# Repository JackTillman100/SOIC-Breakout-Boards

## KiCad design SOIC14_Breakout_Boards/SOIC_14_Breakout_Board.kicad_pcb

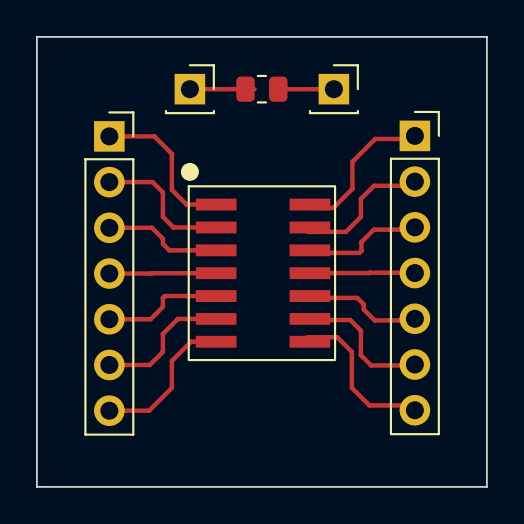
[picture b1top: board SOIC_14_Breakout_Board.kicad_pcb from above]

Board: 2 copper layers, 25.0 x 25.0 mm, 6 parts (0 on the bottom side), 16 nets.

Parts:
J1, J2: Conn_01x07; PinSocket_1x07_P2.54mm_Vertical
J3, J4: Conn_01x01; PinSocket_1x01_P2.54mm_Vertical
R1: R_US; R_0805_2012Metric
SOIC14: 14_Pin_SOIC_Board

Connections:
unnamed: J1.1, SOIC14.1
unnamed: J1.2, SOIC14.2
unnamed: J1.3, SOIC14.3
unnamed: J1.4, SOIC14.4
unnamed: J1.5, SOIC14.5
unnamed: J1.6, SOIC14.6
unnamed: J1.7, SOIC14.7
unnamed: J2.1, SOIC14.14
unnamed: J2.2, SOIC14.13
unnamed: J2.3, SOIC14.12
unnamed: J2.4, SOIC14.11
unnamed: J2.5, SOIC14.10
unnamed: J2.6, SOIC14.9
unnamed: J2.7, SOIC14.8
unnamed: J3.1, R1.2
unnamed: J4.1, R1.1

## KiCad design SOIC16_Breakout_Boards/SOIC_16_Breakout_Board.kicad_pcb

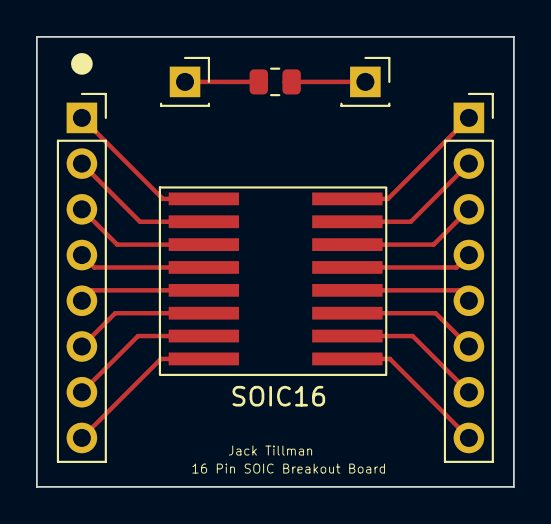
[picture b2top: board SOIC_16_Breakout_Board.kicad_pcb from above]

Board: 2 copper layers, 26.5 x 25.0 mm, 6 parts (0 on the bottom side), 18 nets.

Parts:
J1, J2: Conn_01x08; PinSocket_1x08_P2.54mm_Vertical
J3, J4: Conn_01x01; PinSocket_1x01_P2.54mm_Vertical
R1: R_US; R_0805_2012Metric
SOIC16: 16_Pin_SOIC_Board

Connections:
unnamed: J1.1, SOIC16.1
unnamed: J1.2, SOIC16.2
unnamed: J1.3, SOIC16.3
unnamed: J1.4, SOIC16.4
unnamed: J1.5, SOIC16.5
unnamed: J1.6, SOIC16.6
unnamed: J1.7, SOIC16.7
unnamed: J1.8, SOIC16.8
unnamed: J2.1, SOIC16.16
unnamed: J2.2, SOIC16.15
unnamed: J2.3, SOIC16.14
unnamed: J2.4, SOIC16.13
unnamed: J2.5, SOIC16.12
unnamed: J2.6, SOIC16.11
unnamed: J2.7, SOIC16.10
unnamed: J2.8, SOIC16.9
unnamed: J3.1, R1.2
unnamed: J4.1, R1.1

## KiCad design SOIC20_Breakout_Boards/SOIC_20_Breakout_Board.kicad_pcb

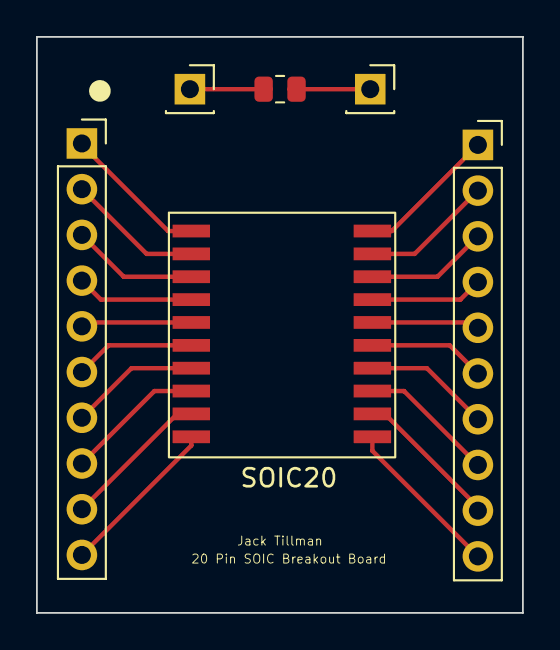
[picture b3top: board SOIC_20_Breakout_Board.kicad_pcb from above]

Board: 2 copper layers, 27.0 x 32.0 mm, 6 parts (0 on the bottom side), 22 nets.

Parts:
J1, J2: Conn_01x10; PinSocket_1x10_P2.54mm_Vertical
J3, J4: Conn_01x01; PinSocket_1x01_P2.54mm_Vertical
R1: R_US; R_0805_2012Metric
SOIC20: 20_Pin_SOIC_Board

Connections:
unnamed: J1.1, SOIC20.1
unnamed: J1.2, SOIC20.2
unnamed: J1.3, SOIC20.3
unnamed: J1.4, SOIC20.4
unnamed: J1.5, SOIC20.5
unnamed: J1.6, SOIC20.6
unnamed: J1.7, SOIC20.7
unnamed: J1.8, SOIC20.8
unnamed: J1.9, SOIC20.9
unnamed: J1.10, SOIC20.10
unnamed: J2.1, SOIC20.20
unnamed: J2.2, SOIC20.19
unnamed: J2.3, SOIC20.18
unnamed: J2.4, SOIC20.17
unnamed: J2.5, SOIC20.16
unnamed: J2.6, SOIC20.15
unnamed: J2.7, SOIC20.14
unnamed: J2.8, SOIC20.13
unnamed: J2.9, SOIC20.12
unnamed: J2.10, SOIC20.11
unnamed: J3.1, R1.2
unnamed: J4.1, R1.1

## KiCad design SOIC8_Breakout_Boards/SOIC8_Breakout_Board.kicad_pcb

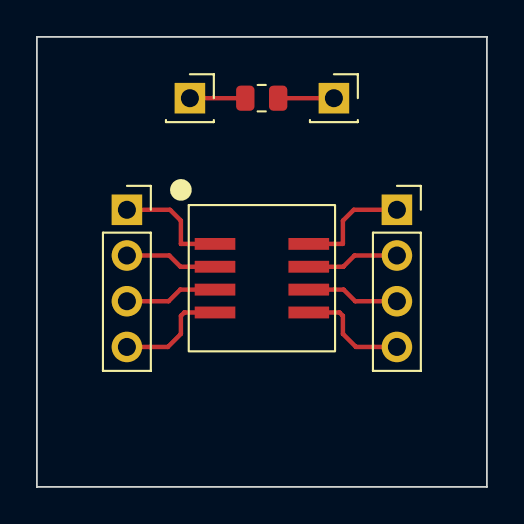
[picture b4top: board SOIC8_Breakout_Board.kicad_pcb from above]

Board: 2 copper layers, 25.0 x 25.0 mm, 6 parts (0 on the bottom side), 10 nets.

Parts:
J1, J2: Conn_01x04; PinSocket_1x04_P2.54mm_Vertical
J3, J4: Conn_01x01; PinSocket_1x01_P2.54mm_Vertical
R1: R_US; R_0805_2012Metric
SOIC8: 8_Pin_SOIC_Board

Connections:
unnamed: J1.1, SOIC8.1
unnamed: J1.2, SOIC8.2
unnamed: J1.3, SOIC8.3
unnamed: J1.4, SOIC8.4
unnamed: J2.1, SOIC8.8
unnamed: J2.2, SOIC8.7
unnamed: J2.3, SOIC8.6
unnamed: J2.4, SOIC8.5
unnamed: J3.1, R1.2
unnamed: J4.1, R1.1

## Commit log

2023-04-05 SOIC8 KiCad Project
    Added schematic, pcb, and project KiCad files for the SOIC8 Breakout Board
2023-04-12 Created KiCad Projects for 14, 16, & 20 Pin Boards
    Created individual folders for each type of SOIC breakout board (8, 14, 16, 20) and created the symbols and schematics necessary for each one. My next commit will be the finalized PCB designs for eac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
2023-04-12 Created PCB designs for the 14, 16 & 20 pic SOIC's
    Finalized and committed pcb designs for the 14, 16, and 20 SOIC breakout boards
2023-04-12 Fixed warnings on all SOIC boards
    Ensured that silkscreen traces didn't intersect solder masks and name/board information is visible on the front of the board rather than the back
2023-04-14 Finished tracing the SOIC20 board
2023-05-09 used as reference (0 noticeable changes)
